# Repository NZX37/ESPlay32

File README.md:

# ESPlay32

## Introduction

### What it is:

A small game console powered by seeed studio xiao esp32 c3, using an accelerometer(which offers a lot of interesting ideas), a tft display and joystick module, which features built in buzzer, battery slots and power switch and LED.

### How to use:

Using the pinouts in the schematic, you can upload code easily via arduino IDE. A few sample games will be made available soon.

The BOM provides links to the screen, joystick and accelerometer.

### Why make?

This started as a small game console i made WAY BACK(when i did my first CAD case!!) on a perfboard with a small OLED and buttons. I was hoping to upgrade it to a joystick and TFT, add an acceleromter(for cool mechanics), as well as use a PCB, buzzer and make use of the esp32's capabilities.

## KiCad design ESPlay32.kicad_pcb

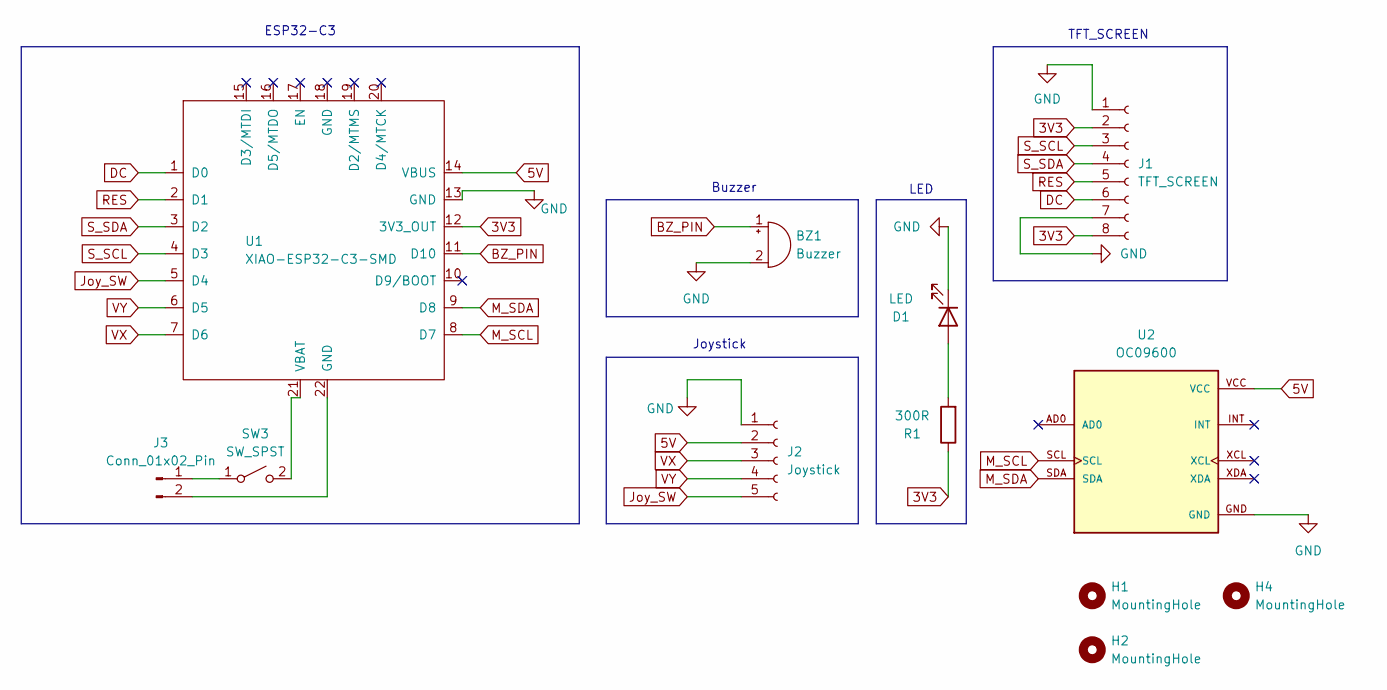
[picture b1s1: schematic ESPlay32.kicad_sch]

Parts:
BZ1: Buzzer; Buzzer_12x9.5RM7.6
D1: LED; LED_D3.0mm
H1, H2, H4: MountingHole; MountingHole_3.2mm_M3
J1: TFT_SCREEN; PinSocket_1x08_P2.54mm_Vertical
J2: Joystick; PinSocket_1x05_P2.54mm_Horizontal
J3: Conn_01x02_Pin; PinHeader_1x02_P2.54mm_Vertical
R1: 300R; R_Axial_DIN0207_L6.3mm_D2.5mm_P7.62mm_Horizontal
SW3: SW_SPST; SW_DIP_SPSTx01_Slide_9.78x4.72mm_W7.62mm_P2.54mm
U1: XIAO-ESP32-C3-SMD; XIAO-ESP32-C3-DIP-SMD
U2: OC09600; MODULE_OC09600; PARTREV NA

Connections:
3V3: J1.2, J1.8, R1.1, U1.12 (3V3_OUT)
5V: J2.2, U1.14 (VBUS), U2.VCC
BZ_PIN: BZ1.1 (+), U1.11 (D10)
DC: J1.6, U1.1 (D0)
GND: BZ1.2 (-), D1.1 (K), J1.1, J1.7, J2.1, U1.13 (GND), U2.GND
Joy_SW: J2.5, U1.5 (D4)
M_SCL: U1.8 (D7), U2.SCL
M_SDA: U1.9 (D8), U2.SDA
unnamed: D1.2 (A), R1.2
unnamed: J3.1, SW3.1 (A)
unnamed: J3.2, U1.22 (GND)
unnamed: SW3.2 (B), U1.21 (VBAT)
RES: J1.5, U1.2 (D1)
S_SCL: J1.3, U1.4 (D3)
S_SDA: J1.4, U1.3 (D2)
VX: J2.3, U1.7 (D6)
VY: J2.4, U1.6 (D5)

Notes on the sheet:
ESP32-C3
TFT_SCREEN
Joystick
LED
Buzzer

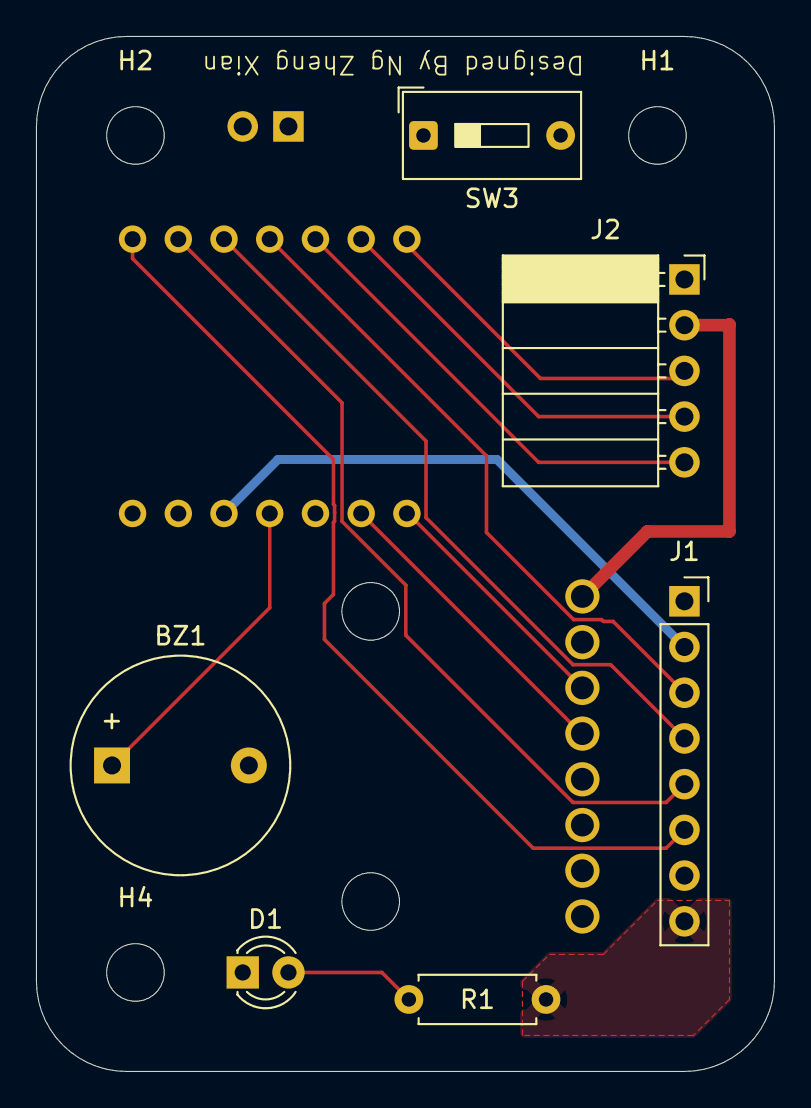
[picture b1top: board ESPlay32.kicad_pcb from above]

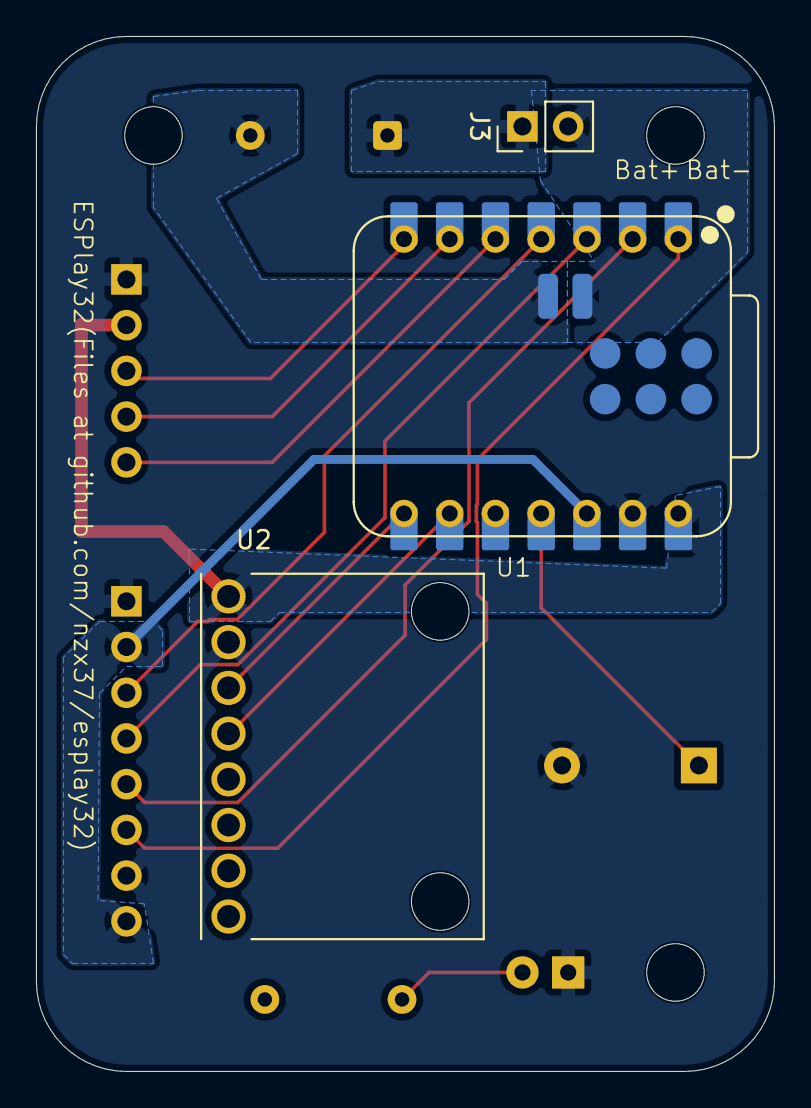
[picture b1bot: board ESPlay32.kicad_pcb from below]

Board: 2 copper layers, 41.0 x 57.5 mm, 12 parts (3 on the bottom side), 17 nets.
